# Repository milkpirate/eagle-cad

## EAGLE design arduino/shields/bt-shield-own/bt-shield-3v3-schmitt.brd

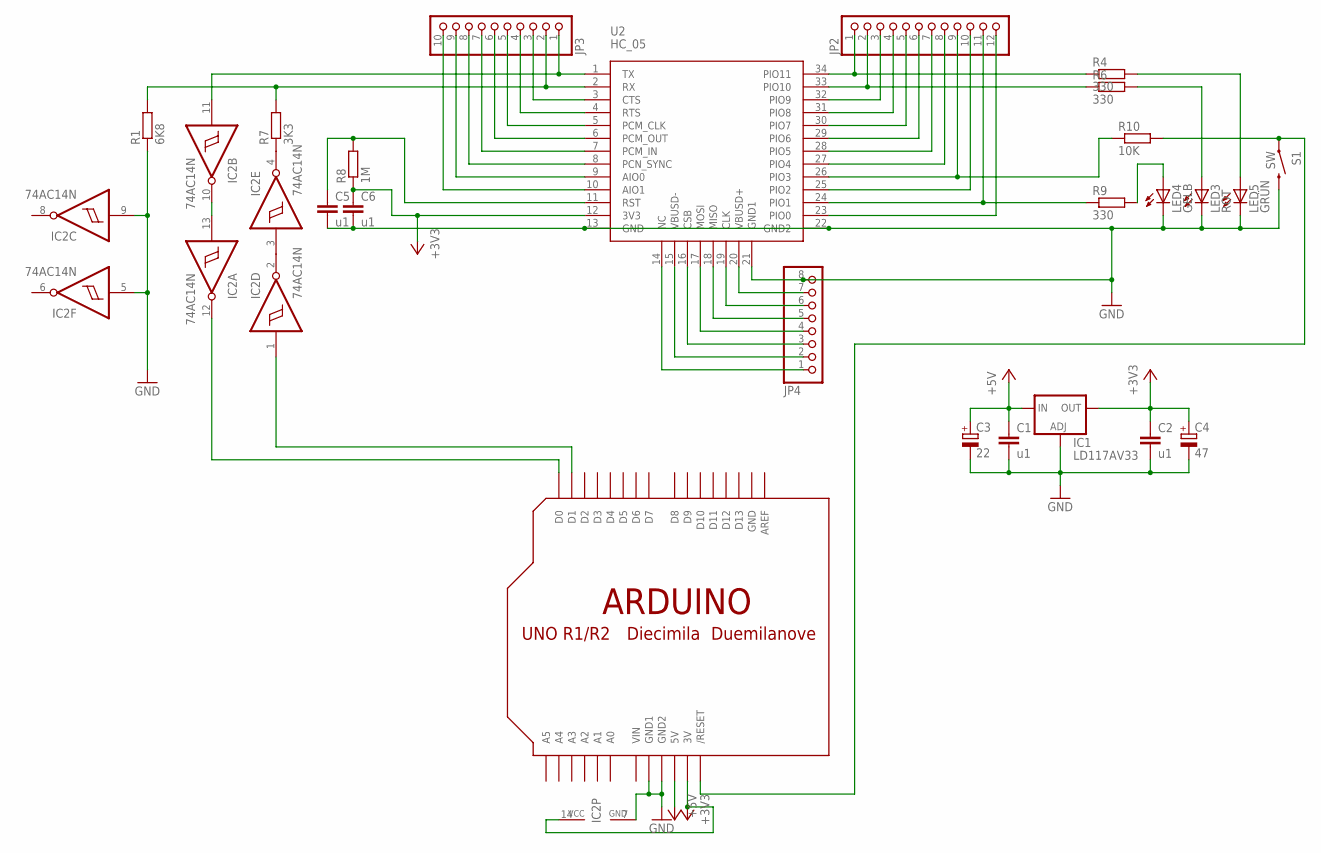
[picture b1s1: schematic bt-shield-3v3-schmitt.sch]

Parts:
C1, C2, C5, C6: u1; C025-025X050
C3: 22; E2,5-5
C4: 47; E2,5-5
IC1: LD117AV33; TO220L1
IC2: 74AC14N; DIL14
JP2: PINHD-1X12; 1X12
JP3: PINHD-1X10; 1X10
JP4: PINHD-1X8; 1X08
LED3: ROT; LED5MM
LED4: GELB; LED5MM
LED5: GRÜN; LED5MM
R1: 6K8; 0204/7
R4, R6, R9: 330; 0207/2V
R7: 3K3; 0204/7
R8: 1M; 0204/7
R10: 10K; 0207/10
S1: SW; TACTILE-PTH
U2: HC_05; BLUETOOTH_SMD
U$1: ARDUINO-NOHOLE

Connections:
+3V3: C2.1, C4.+, C6.1, IC1.2 (OUT), IC2.14 (VCC), R8.1, U2.12 (3V3), U$1.3V
+5V: C1.1, C3.+, IC1.3 (IN), U$1.5V
GND: C1.2, C2.2, C3.-, C4.-, C5.2, C6.2, IC1.1 (ADJ), IC2.5 (I), IC2.7 (GND), IC2.9 (I), JP4.8, LED3.K (C), LED4.K (C), LED5.K (C), R1.1, S1.3 (2), U2.13 (GND), U2.21 (GND1), U2.22 (GND2), U$1.GND, U$1.GND1, U$1.GND2
unnamed: IC2.12 (O), U$1.D0
unnamed: R10.2, S1.1, U$1.RESET (/RESET)
unnamed: JP3.3, U2.3 (CTS)
unnamed: C5.1, R8.2, U2.11 (RST)
unnamed: JP2.2, R6.1, U2.33 (PIO10)
unnamed: JP2.1, R4.1, U2.34 (PIO11)
unnamed: LED3.A, R6.2
unnamed: LED5.A, R4.2
unnamed: LED4.A, R9.2
unnamed: JP2.11, R9.1, U2.24 (PIO1)
unnamed: JP2.9, R10.1, U2.26 (PIO3)
unnamed: JP3.4, U2.4 (RTS)
unnamed: IC2.10 (O), IC2.13 (I)
unnamed: JP3.5, U2.5 (PCM_CLK)
unnamed: IC2.11 (I), JP3.1, U2.1 (TX)
unnamed: IC2.4 (O), R7.1
unnamed: IC2.2 (O), IC2.3 (I)
unnamed: IC2.1 (I), U$1.D1
unnamed: JP3.2, R1.2, R7.2, U2.2 (RX)
unnamed: JP3.6, U2.6 (PCM_OUT)
unnamed: JP3.7, U2.7 (PCM_IN)
unnamed: JP3.8, U2.8 (PCN_SYNC)
unnamed: JP3.9, U2.9 (AIO0)
unnamed: JP3.10, U2.10 (AIO1)
unnamed: JP2.3, U2.32 (PIO9)
unnamed: JP2.4, U2.31 (PIO8)
unnamed: JP2.5, U2.30 (PIO7)
unnamed: JP2.6, U2.29 (PIO6)
unnamed: JP2.7, U2.28 (PIO5)
unnamed: JP2.8, U2.27 (PIO4)
unnamed: JP2.10, U2.25 (PIO2)
unnamed: JP2.12, U2.23 (PIO0)
unnamed: JP4.7, U2.20 (VBUSD+)
unnamed: JP4.6, U2.19 (CLK)
unnamed: JP4.5, U2.18 (MISO)
unnamed: JP4.3, U2.16 (CSB)
unnamed: JP4.2, U2.15 (VBUSD-)
unnamed: JP4.1, U2.14 (NC)
unnamed: JP4.4, U2.17 (MOSI)
VIN: U$1.VIN

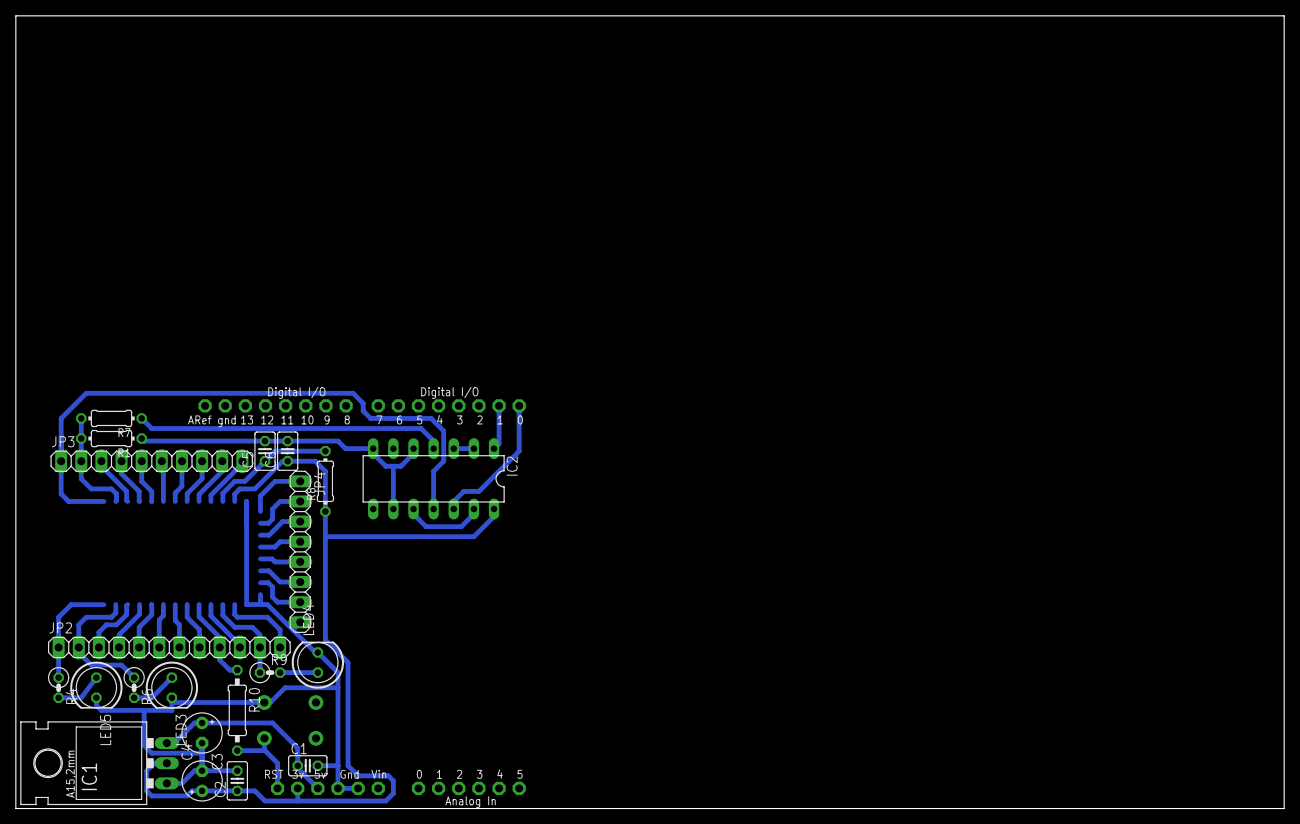
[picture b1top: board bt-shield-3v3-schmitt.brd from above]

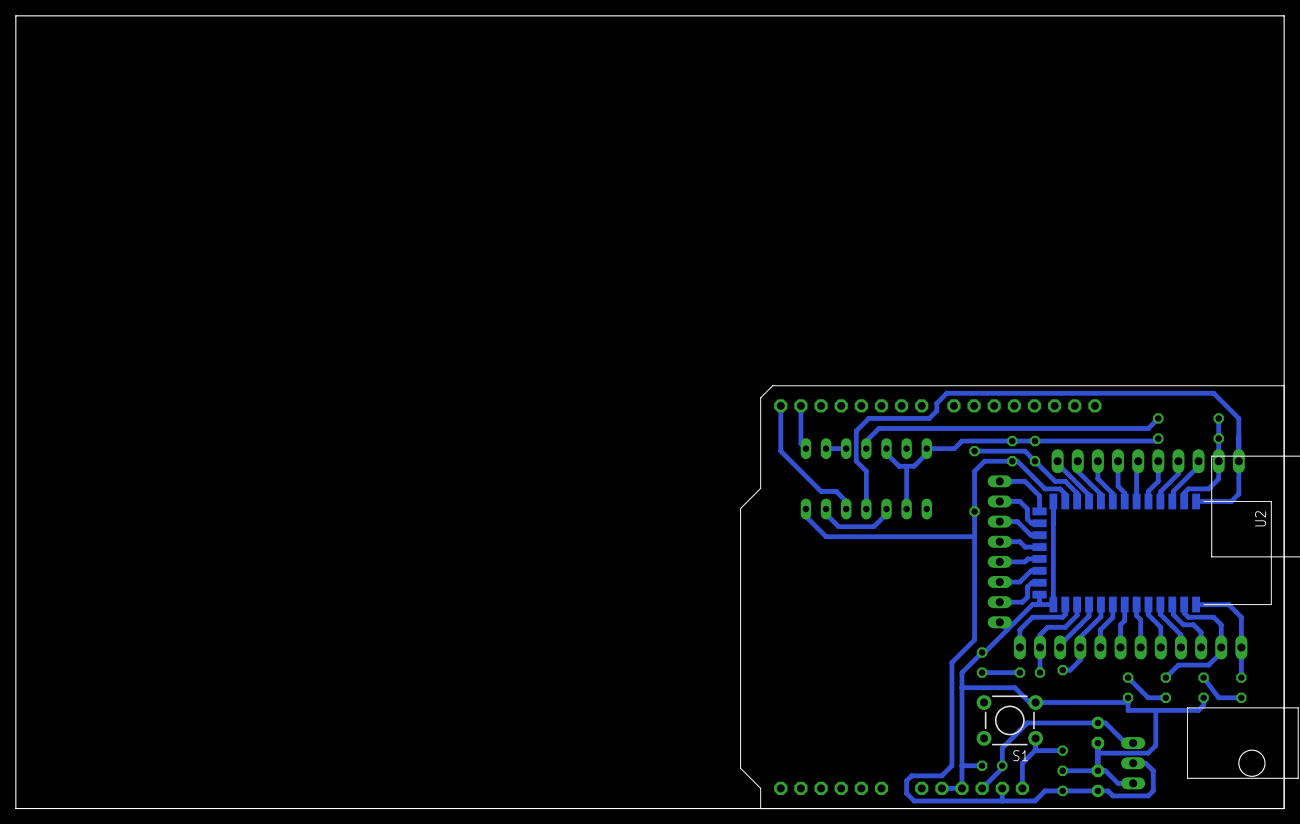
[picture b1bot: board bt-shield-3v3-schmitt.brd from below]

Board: 2 copper layers, 160.0 x 100.0 mm, 24 parts (2 on the bottom side), 42 nets.

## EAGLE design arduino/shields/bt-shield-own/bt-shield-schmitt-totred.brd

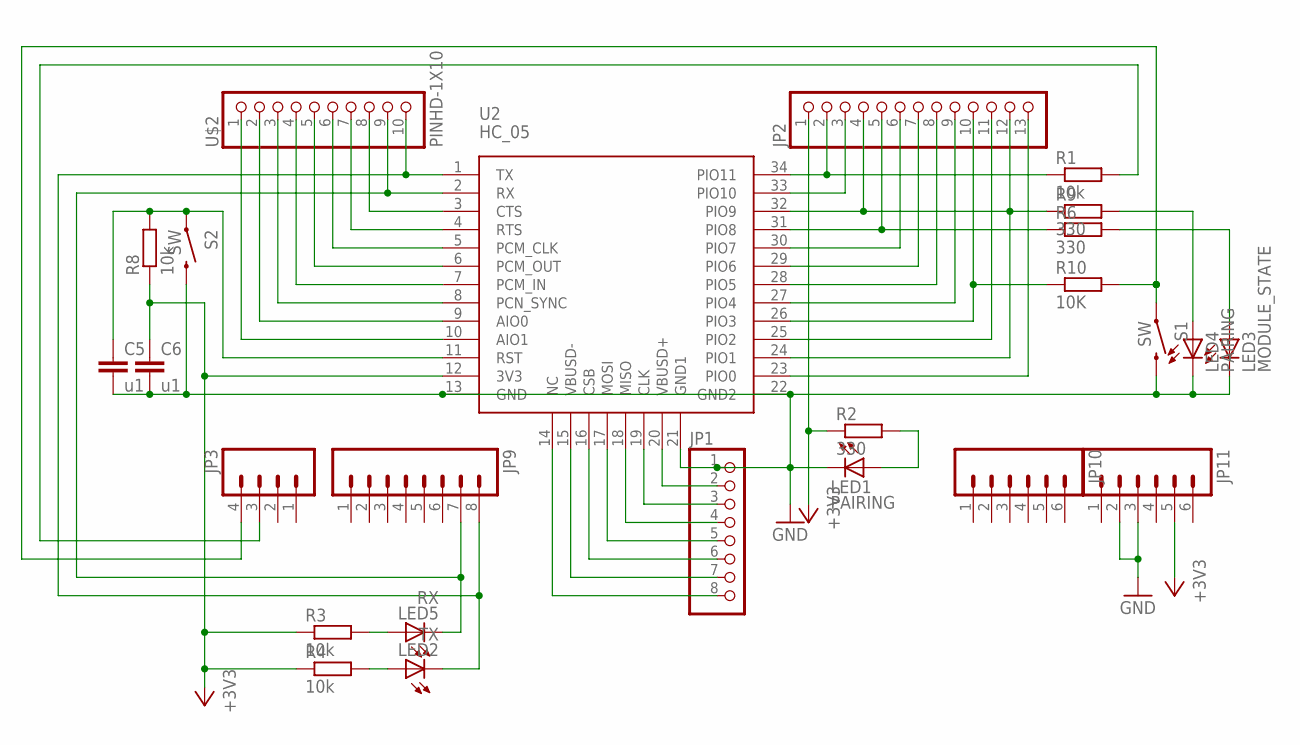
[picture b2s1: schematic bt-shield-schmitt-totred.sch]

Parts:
C5, C6: u1; C025-025X050
JP1: PINHD-1X8BIG; 1X08-BIG
JP2: PINHD-1X13_BIG; 1X13-BIG
JP3: M04POLAR; MOLEX-1X4
JP9: M081X08; 1X08
JP10, JP11: M06SIP; 1X06
LED1, LED4: PAIRING; LED5MM
LED2: TX; LED2X5
LED3: MODULE_STATE; LED5MM
LED5: RX; LED2X5
R1, R3, R4, R8: 10k; 0207/2V
R2, R6, R9: 330; 0204/5
R10: 10K; 0204/7
S1, S2: SW; TACTILE-PTH
U2: HC_05; BLUETOOTH_SMD
U$2: PINHD-1X10; 1X10-BIG

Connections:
+3V3: C6.1, JP2.1, JP11.5, R2.1, R3.1, R4.1, R8.1, U2.12 (3V3)
GND: C5.2, C6.2, JP1.1, JP11.2, JP11.3, LED1.K (C), LED3.K (C), LED4.K (C), S1.3 (2), S2.3 (2), U2.13 (GND), U2.21 (GND1), U2.22 (GND2)
unnamed: JP3.4, R10.2, S1.1
unnamed: JP3.3, R1.2
unnamed: U2.3 (CTS), U$2.8
unnamed: C5.1, R8.2, S2.1, U2.11 (RST)
unnamed: JP2.3, U2.33 (PIO10)
unnamed: LED5.A, R3.2
unnamed: JP2.2, R1.1, U2.34 (PIO11)
unnamed: LED3.A, R6.2
unnamed: LED1.A, R2.2
unnamed: LED4.A, R9.2
unnamed: LED2.A, R4.2
unnamed: JP2.10, R10.1, U2.26 (PIO3)
unnamed: U2.4 (RTS), U$2.7
unnamed: U2.5 (PCM_CLK), U$2.6
unnamed: JP9.8, LED2.K (C), U2.1 (TX), U$2.10
unnamed: JP9.7, LED5.K (C), U2.2 (RX), U$2.9
unnamed: U2.6 (PCM_OUT), U$2.5
unnamed: U2.7 (PCM_IN), U$2.4
unnamed: U2.8 (PCN_SYNC), U$2.3
unnamed: U2.9 (AIO0), U$2.2
unnamed: U2.10 (AIO1), U$2.1
unnamed: JP2.4, JP2.12, R9.1, U2.24 (PIO1), U2.32 (PIO9)
unnamed: JP2.5, R6.1, U2.31 (PIO8)
unnamed: JP2.6, U2.30 (PIO7)
unnamed: JP2.7, U2.29 (PIO6)
unnamed: JP2.8, U2.28 (PIO5)
unnamed: JP2.9, U2.27 (PIO4)
unnamed: JP2.11, U2.25 (PIO2)
unnamed: JP2.13, U2.23 (PIO0)
unnamed: JP1.2, U2.20 (VBUSD+)
unnamed: JP1.3, U2.19 (CLK)
unnamed: JP1.4, U2.18 (MISO)
unnamed: JP1.6, U2.16 (CSB)
unnamed: JP1.7, U2.15 (VBUSD-)
unnamed: JP1.8, U2.14 (NC)
unnamed: JP1.5, U2.17 (MOSI)

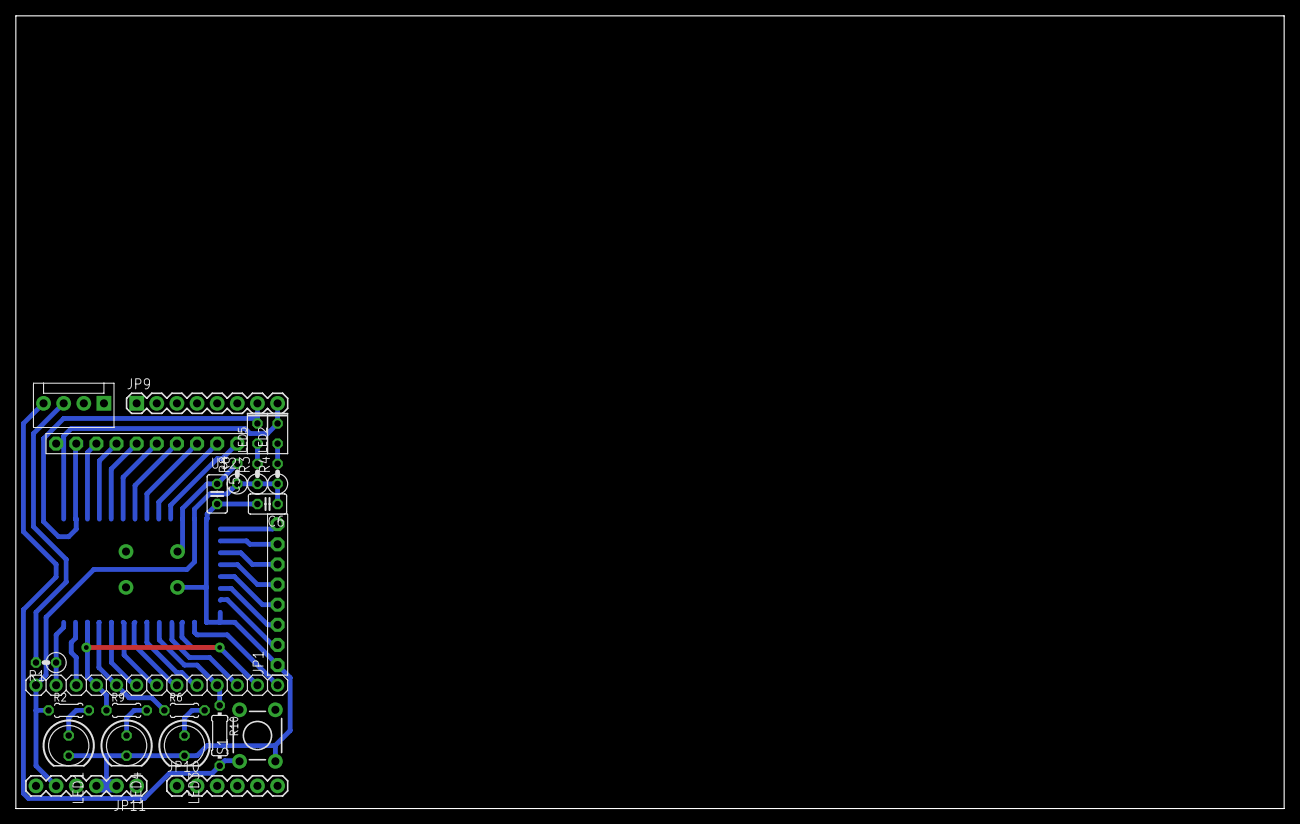
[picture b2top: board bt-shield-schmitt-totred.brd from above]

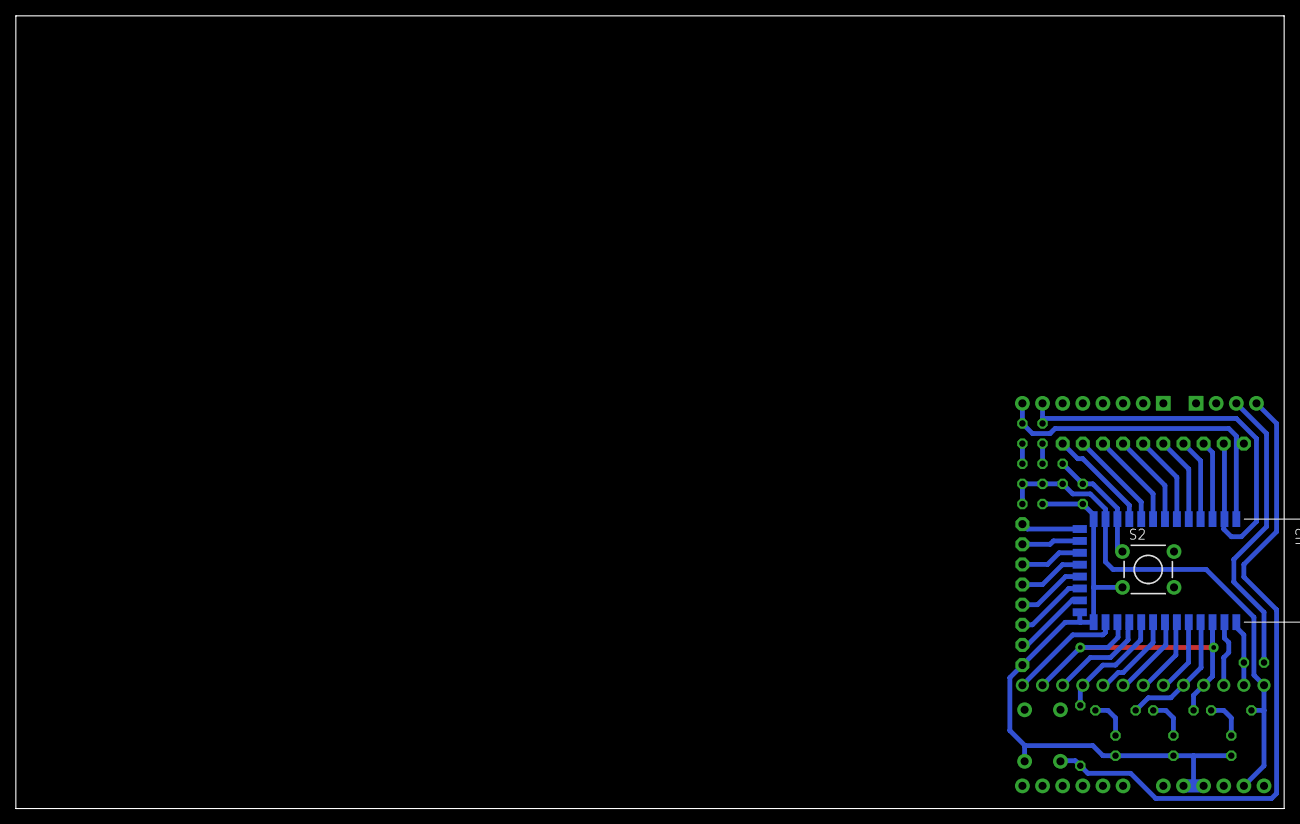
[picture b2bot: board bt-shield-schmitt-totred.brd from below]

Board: 2 copper layers, 160.0 x 100.0 mm, 25 parts (2 on the bottom side), 38 nets.

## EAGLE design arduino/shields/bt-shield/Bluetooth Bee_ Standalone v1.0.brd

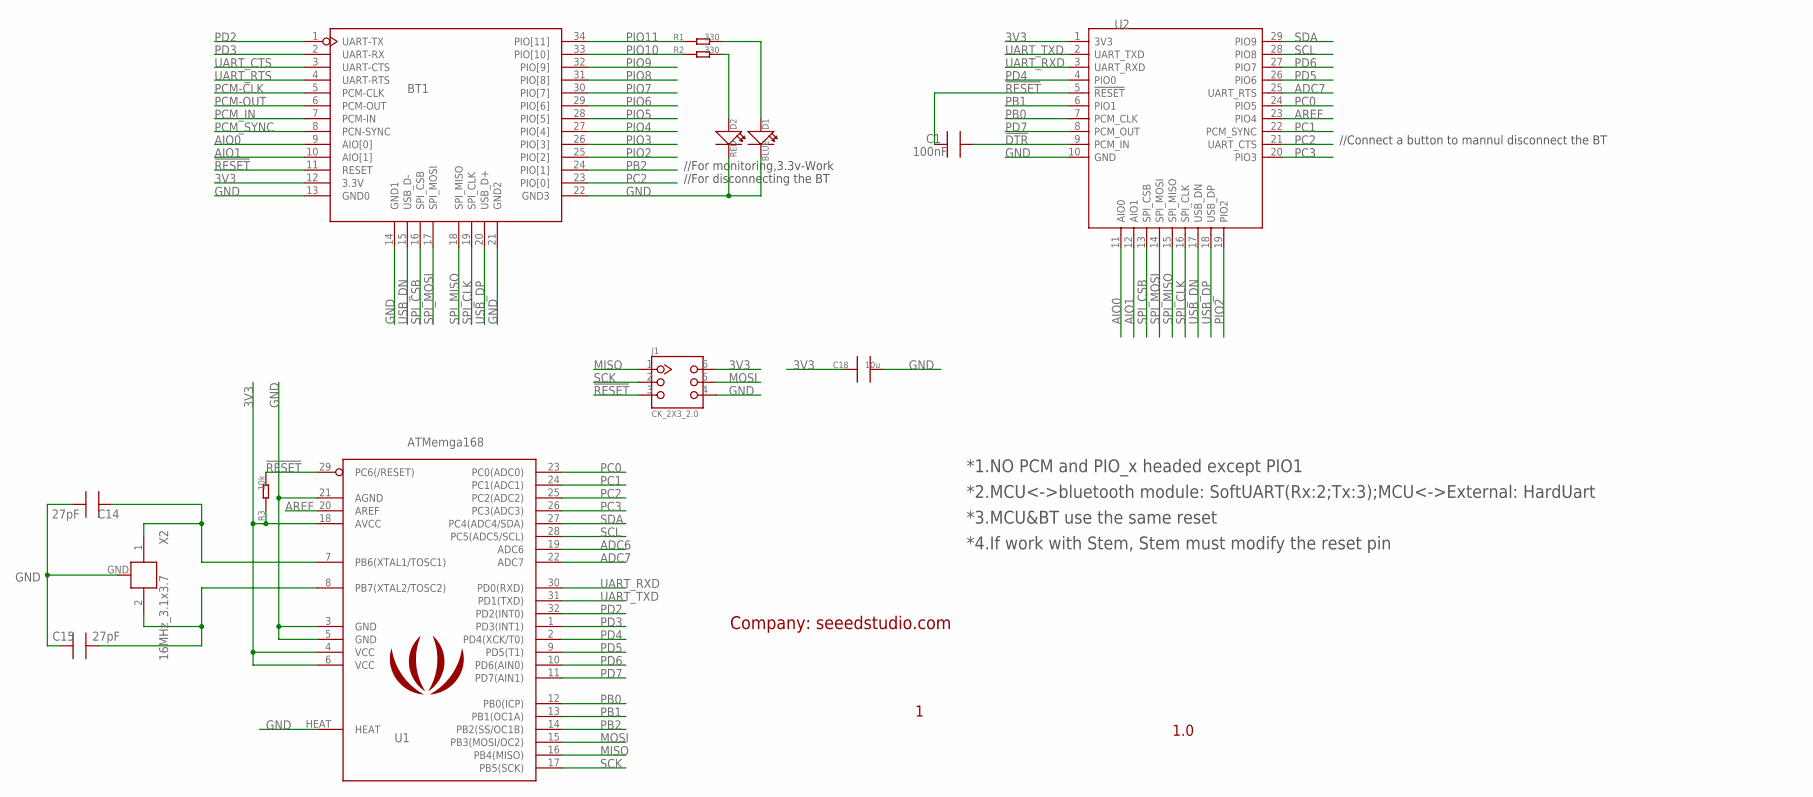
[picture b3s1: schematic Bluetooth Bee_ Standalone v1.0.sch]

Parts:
BT1: SERIAL_BLUETEETHSMT; SERIAL_BLUETEETH
C1: 100nF; 0603_S
C14, C15: 27pF; 0603
C18: 10u; 0805
D1: BLUE; LED0603
D2: RED; LED0603
J1: CK_2X3_2.0
LOGO1: LOGO_SILK
R1, R2: 330; 0603
R3: 10k; 0603_S@1
U1: ATMemga168; MLF32X
U2: BLUTOOTHBEE-MS; 29P-DIP-2.0
X2: 16MHz_3.1x3.7; XTAL_NC

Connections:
3V3: BT1.12 (3.3V), C18.1, J1.6, R3.1, U1.4 (VCC), U1.6 (VCC), U1.18 (AVCC), U2.1 (3V3)
!DTR: C1.1, U2.9 (PCM_IN)
!RESET: BT1.11 (RESET), C1.2, J1.3, R3.2, U1.29 (PC6(/RESET)), U2.5 (!RESET)
ADC6: U1.19 (ADC6)
ADC7: U1.22 (ADC7), U2.25 (UART_RTS)
AIO0: BT1.9 (AIO[0]), U2.11 (AIO0)
AIO1: BT1.10 (AIO[1]), U2.12 (AIO1)
AREF: U1.20 (AREF), U2.23 (PIO4)
GND: BT1.13 (GND0), BT1.14 (GND1), BT1.21 (GND2), BT1.22 (GND3), C14.2, C15.1, C18.2, D1.2 (-), D2.2 (-), J1.4, U1.3 (GND), U1.5 (GND), U1.21 (AGND), U1.HEAT, U2.10 (GND), X2.GND
MISO: J1.1, U1.16 (PB4(MISO))
MOSI: J1.5, U1.15 (PB3(MOSI/OC2))
unnamed: D2.1 (+), R2.2
unnamed: D1.1 (+), R1.2
PB0: U1.12 (PB0(ICP)), U2.7 (PCM_CLK)
PB1: U1.13 (PB1(OC1A)), U2.6 (PIO1)
PB2: BT1.24 (PIO[1]), U1.14 (PB2(SS/OC1B))
PC0: U1.23 (PC0(ADC0)), U2.24 (PIO5)
PC1: U1.24 (PC1(ADC1)), U2.22 (PCM_SYNC)
PC2: BT1.23 (PIO[0]), U1.25 (PC2(ADC2)), U2.21 (UART_CTS)
PC3: U1.26 (PC3(ADC3)), U2.20 (PIO3)
PCM-CLK: BT1.5 (PCM-CLK)
PCM-OUT: BT1.6 (PCM-OUT)
PCM_IN: BT1.7 (PCM-IN)
PCM_SYNC: BT1.8 (PCN-SYNC)
PD2: BT1.1 (UART-TX), U1.32 (PD2(INT0))
PD3: BT1.2 (UART-RX), U1.1 (PD3(INT1))
PD4: U1.2 (PD4(XCK/T0)), U2.4 (PIO0)
PD5: U1.9 (PD5(T1)), U2.26 (PIO6)
PD6: U1.10 (PD6(AIN0)), U2.27 (PIO7)
PD7: U1.11 (PD7(AIN1)), U2.8 (PCM_OUT)
PIO2: BT1.25 (PIO[2]), U2.19 (PIO2)
PIO3: BT1.26 (PIO[3])
PIO4: BT1.27 (PIO[4])
PIO5: BT1.28 (PIO[5])
PIO6: BT1.29 (PIO[6])
PIO7: BT1.30 (PIO[7])
PIO8: BT1.31 (PIO[8])
PIO9: BT1.32 (PIO[9])
PIO10: BT1.33 (PIO[10]), R2.1
PIO11: BT1.34 (PIO[11]), R1.1
SCK: J1.2, U1.17 (PB5(SCK))
SCL: U1.28 (PC5(ADC5/SCL)), U2.28 (PIO8)
SDA: U1.27 (PC4(ADC4/SDA)), U2.29 (PIO9)
SPI_CLK: BT1.19 (SPI_CLK), U2.16 (SPI_CLK)
SPI_CSB: BT1.16 (SPI_CSB), U2.13 (SPI_CSB)
SPI_MISO: BT1.18 (SPI_MISO), U2.15 (SPI_MISO)
SPI_MOSI: BT1.17 (SPI_MOSI), U2.14 (SPI_MOSI)
UART_CTS: BT1.3 (UART-CTS)
UART_RTS: BT1.4 (UART-RTS)
UART_RXD: U1.30 (PD0(RXD)), U2.3 (UART_RXD)
UART_TXD: U1.31 (PD1(TXD)), U2.2 (UART_TXD)
USB_DN: BT1.15 (USB_D-), U2.17 (USB_DN)
USB_DP: BT1.20 (USB_D+), U2.18 (USB_DP)
XTAL1: C14.1, U1.7 (PB6(XTAL1/TOSC1)), X2.1
XTAL2: C15.2, U1.8 (PB7(XTAL2/TOSC2)), X2.2

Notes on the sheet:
1.0
Company: seeedstudio.com
//For disconnecting the BT
*1.NO PCM and PIO_x headed except PIO1
*2.MCU<->bluetooth module: SoftUART(Rx:2;Tx:3);MCU<->External: HardUart
//For monitoring,3.3v-Work
*3.MCU&BT use the same reset
*4.If work with Stem, Stem must modify the reset pin
//Connect a button to mannul disconnect the BT

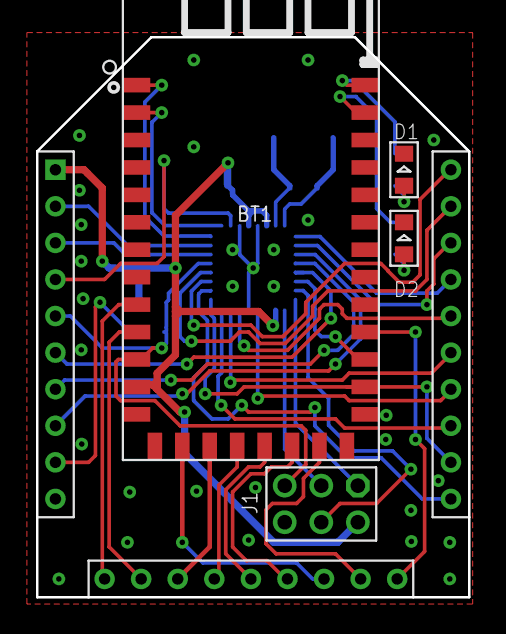
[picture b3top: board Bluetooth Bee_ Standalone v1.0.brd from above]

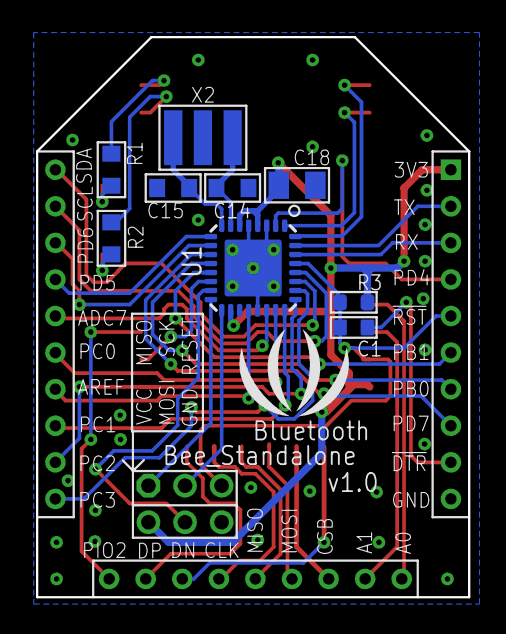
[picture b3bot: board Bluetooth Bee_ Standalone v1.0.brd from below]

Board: 2 copper layers, 24.0 x 31.1 mm, 15 parts (10 on the bottom side), 41 nets.

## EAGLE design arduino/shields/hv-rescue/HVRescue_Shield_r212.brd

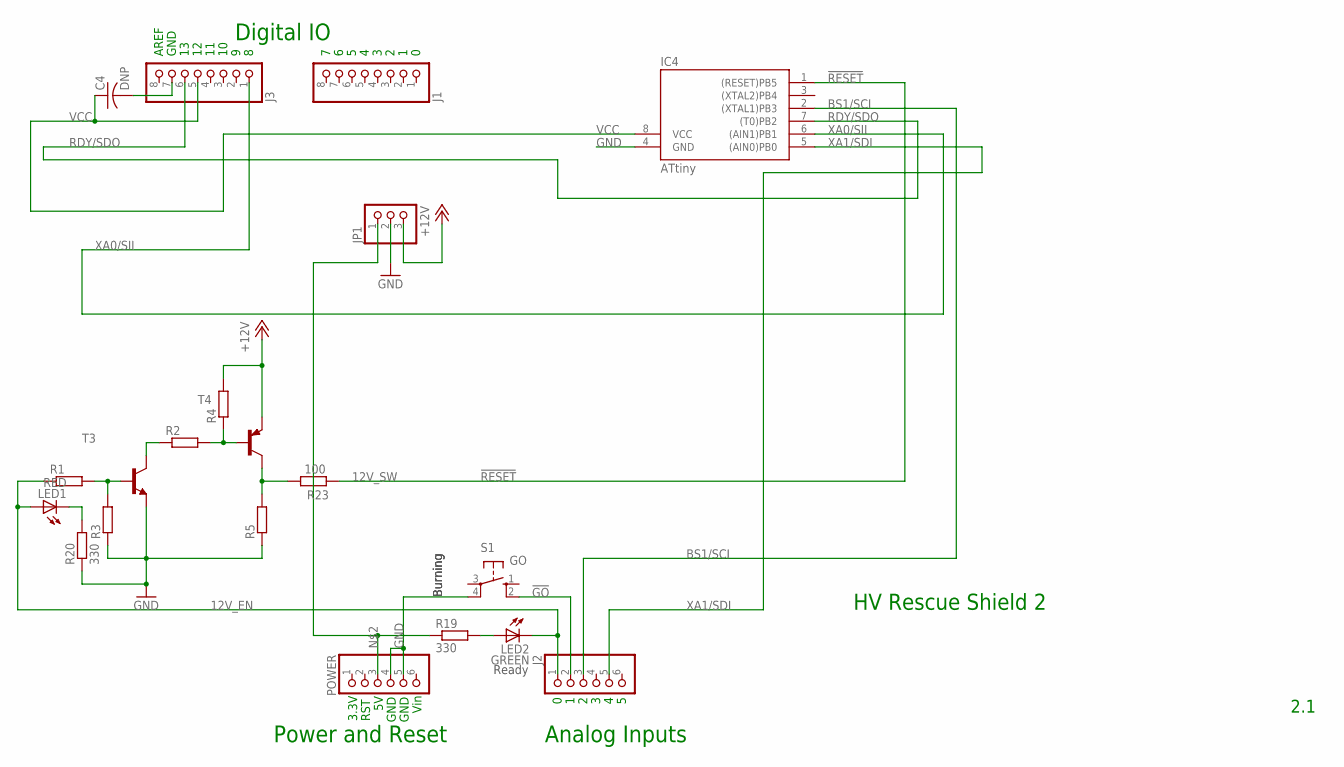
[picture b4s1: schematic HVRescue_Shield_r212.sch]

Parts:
C4: DNP; C025-025X050
IC4: ATtiny; DIL08
J1, J3: PINHD-1X8; 1X08
J2: PINHD-1X6; 1X06
JP1: PINHD-1X3; 1X03
LED1: RED; LED3MM
LED2: GREEN; LED3MM
POWER: PINHD-1X6; 1X06
R1, R2, R3, R4, R5: R-EU_0207/7; 0207/7
R19, R20: 330; 0207/7
R23: 100; 0207/7
S1: GO; B3F-10XX
T3: -NPN-TO92-ECB; TO92-ECB
T4: -PNP-TO92-CEB; TO92-CEB

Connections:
12V_EN: J2.1, LED1.A, LED2.K (C), R1.1
12V_SW: R5.2, R23.1, T4.C
!GO: J2.2, S1.2 (S1)
!RESET: IC4.1 ((RESET)PB5), R23.2
+12V: JP1.3, R4.2, T4.E
BS1/SCI: IC4.2 ((XTAL1)PB3), J2.3
GND: IC4.4 (GND), JP1.2, POWER.4, POWER.5, R3.1, R5.1, R20.1, S1.4 (P1), T3.E
unnamed: LED1.K (C), R20.2
unnamed: JP1.1, POWER.3, R19.1
unnamed: R1.2, R3.2, T3.B
unnamed: R2.1, T3.C
unnamed: R2.2, R4.1, T4.B
unnamed: LED2.A, R19.2
unnamed: C4.2, J3.7
RDY/SDO: IC4.7 ((T0)PB2), J3.6
VCC: C4.1, IC4.8 (VCC), J3.5
XA0/SII: IC4.6 ((AIN1)PB1), J3.1
XA1/SDI: IC4.5 ((AIN0)PB0), J2.5

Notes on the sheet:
2.1
HV Rescue Shield 2
Analog Inputs
Power and Reset
Digital IO
Vin
GND
RST
3.3V
AREF
Ready
Burning

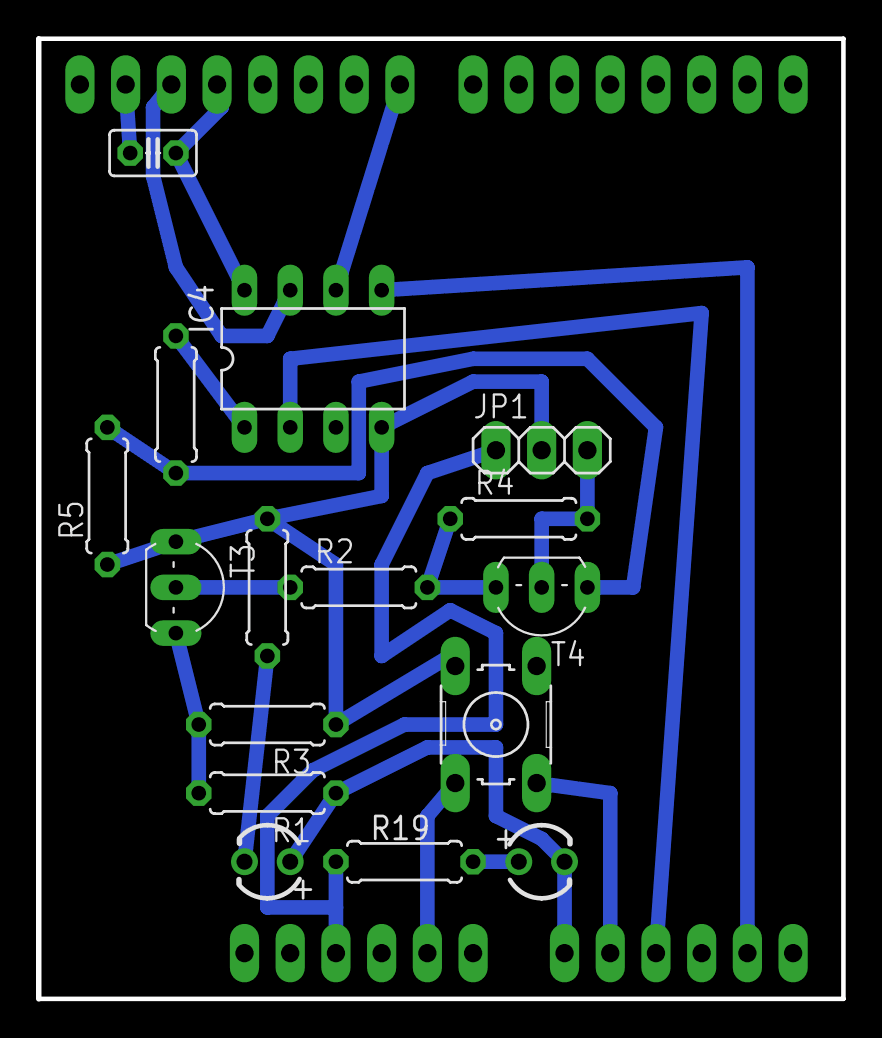
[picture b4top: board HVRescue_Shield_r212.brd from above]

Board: 2 copper layers, 44.7 x 53.3 mm, 20 parts (0 on the bottom side), 18 nets.

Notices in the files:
parts and their libraries:
SparkFun: Licensing: CC v3.0 Share-Alike You are welcome to use this library for commercial purposes.
